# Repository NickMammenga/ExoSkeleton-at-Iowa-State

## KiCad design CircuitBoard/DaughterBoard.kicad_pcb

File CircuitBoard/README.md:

# Exoskeleton control board documentation
## Created and written by Parker K
### 11/12/26

## Mother Board
The mother board has two primary jobs. It first takes in the 48V battery and distributes it to both motors while converting down to 5V for the rest of the board. It also contains the microcontroller that runs the control loop and takes in data from the sensors.

The power section uses a mostly stock example circuit from the LMR38020. This takes 48V down to 5V using a switching regulator. The only important thing to note is that the power filter capacitors on the battery need to be 100V rated, and the SMD fuses are set at 20amp. The motor has a nominal current draw of 8amps, and a peak of 24amps. By using a time delay 20amp fuse it makes sure the motors never draw enough current to damage them.

On the board design, the motors are connected by using large ground pours. It is recommended to use 2oz copper to manage the heat and current when manufacturing the boards but as of writing, this has not be tested.

The 5V is then routed into the 5Vin pin of the microcontroller which then converts it into 3.3V. (this uses the internal 5v to 3.3v regulator it has because of the USB). This saves space, but it means that the battery can not be plugged in at the same time the microcontroller is.

Finally there are some integrated sensors that the MCU draws from and CAN outputs. The motors work over CAN bus, and the Waveshare CAN module is used as the can transceiver.

## Daughter Board
In order to better fit the exoskeleton, the mother board is designed to be mounted on the back plate. The daughter board is then designed to house the user controls and be mounted on the front with a cable connecting the two. It contains an 8 position rotary switch, a potentiometer, and an RGB LED. The rotary switch can be used to change the mode the exoskeleton operates in, while the pot can control strength,

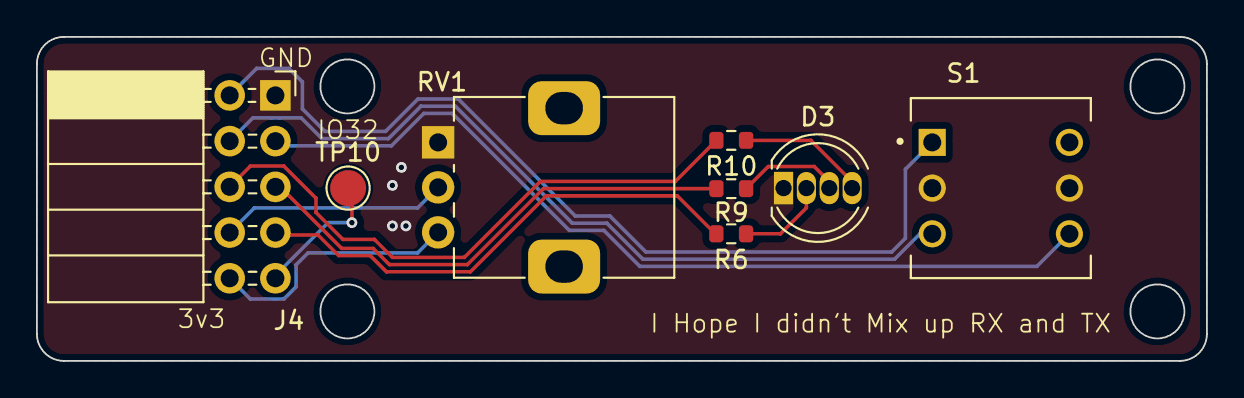
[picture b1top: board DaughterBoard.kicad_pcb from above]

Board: 2 copper layers, 65.0 x 18.0 mm, 8 parts (0 on the bottom side), 13 nets.

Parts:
D3: LED_KRGB; LED_D5.0mm-4_RGB
J4: Conn_01x10_Pin; PinSocket_2x05_P2.54mm_Horizontal
R6, R9, R10: 220; R_0603_1608Metric
RV1: 10KO; Potentiometer_Alps_RK09K_Single_Vertical
S1: RDS3-8S-1065-3-D; SW_RDS3-8S-1065-3-D
TP10: TestPoint; TestPoint_Pad_D2.0mm

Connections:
+3.3V: J4.10, RV1.3
GND: D3.1 (K), J4.1, RV1.1, S1.C1 (C), S1.C2 (C__1)
unnamed: D3.4 (BA), R10.1
unnamed: D3.3 (GA), R9.1
unnamed: D3.2 (RA), R6.1
unnamed: J4.2, S1.1
unnamed: J4.3, S1.2
unnamed: J4.4, S1.4
unnamed: J4.5, R9.2
unnamed: J4.6, R10.2
unnamed: J4.7, R6.2
unnamed: J4.8, RV1.2
unnamed: J4.9, TP10.1 (1_1)

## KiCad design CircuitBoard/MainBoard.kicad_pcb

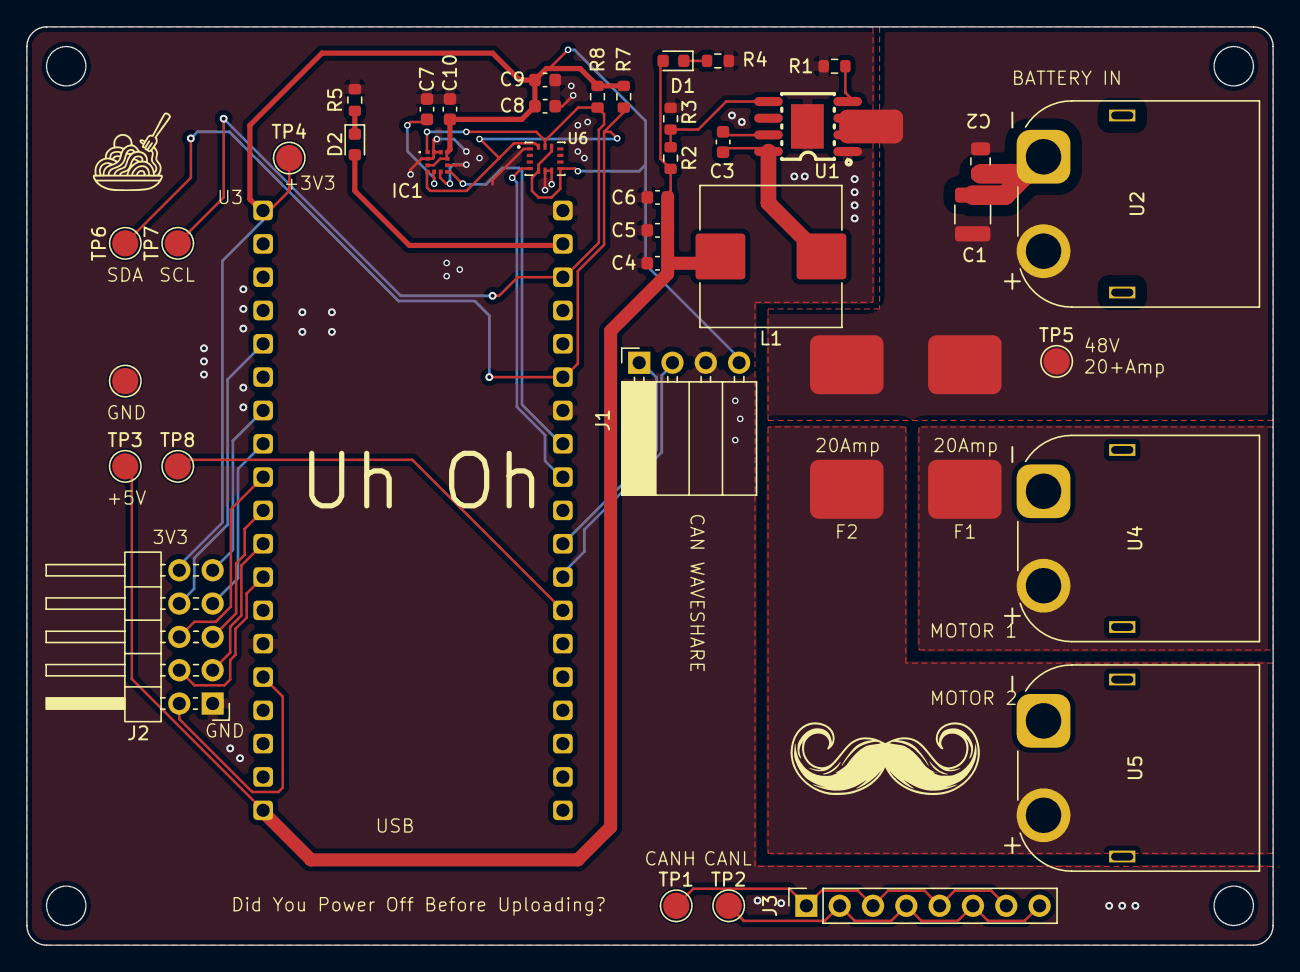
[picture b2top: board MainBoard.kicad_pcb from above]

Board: 2 copper layers, 95.0 x 70.0 mm, 40 parts (0 on the bottom side), 31 nets.

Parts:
C1: 4.7uF; C_1210_3225Metric
C2: 100nF; C_0805_2012Metric
C3, C8, C9, C10: 100nF; C_0603_1608Metric
C4, C5, C6: 22uF; C_0603_1608Metric
C7: 220nF; C_0603_1608Metric
D1, D2: LED; LED_0603_1608Metric
F1, F2: Fuse; SMDFuse MP012924
IC1: IIS2MDCTR
J1: Conn_01x04_Socket; PinSocket_1x04_P2.54mm_Horizontal
J2: Conn_01x10_Pin; PinHeader_2x05_P2.54mm_Horizontal
J3: Conn_01x08_Pin; PinSocket_1x08_P2.54mm_Vertical
L1: 15uH; L_Wuerth_HCI-1030
R1: 64.9kO; R_0603_1608Metric
R2: 100k; R_0603_1608Metric
R3: 24.9k; R_0603_1608Metric
R4, R5: 1k; R_0603_1608Metric
R7: 4.7k; R_0603_1608Metric
R8: 4,7k; R_0603_1608Metric
TP1, TP2, TP3, TP4, TP5, TP6, TP7, TP8: TestPoint; TestPoint_Pad_D2.0mm
U1: LMR38020SQDDARQ1; SOIC-8_L4.9-W3.9-P1.27-LS6.0-BL-EP3.4
U2, U4, U5: XT60; AMASS_XT60PW-M_1x02_P7.20mm_Horizontal
U3: ESP32 38Pin Slim
U6: BMI270; XDCR_BMI270

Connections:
48V: C1.1, C2.1, F1.2, F2.2, TP5.1 (1_1), U1.2 (EN), U1.3 (VIN), U2.2 (+)
+3.3V: C8.1, C9.1, C10.1, IC1.3 (CS), IC1.9 (VDD), IC1.10 (VDD_IO), J1.4, J2.10, R7.1, R8.1, TP4.1 (1_1), U3.1 (3.3V), U6.5 (VDDIO), U6.8 (VDD), U6.12 (CSB)
+5V: C4.1, C5.1, C6.1, D1.2 (A), L1.2, R2.1, TP3.1 (1_1), U3.19 (5.0V_In)
CANH: J3.1, J3.3, J3.5, J3.7, TP1.1 (1_1)
CANL: J3.2, J3.4, J3.6, J3.8, TP2.1 (1_1)
CRX: J1.2, U3.27 (IO16)
CTX: J1.1, U3.28 (IO17)
GND: C1.2, C2.2, C4.2, C5.2, C6.2, C7.1, C8.2, C9.2, C10.2, IC1.2 (NC_1), IC1.6 (GND_1), IC1.8 (GND_2), IC1.11 (NC_2), IC1.12 (NC_3), J1.3, J2.1, R1.2, R3.2, R4.2, R5.2, U1.1 (GND), U1.9 (EP), U2.1 (-), U3.14 (GND), U3.32 (GND), U3.38 (GND), U4.1 (-), U5.1 (-), U6.1 (SDO), U6.6 (GNDIO), U6.7 (GND)
IMUINT: U3.30 (IO18), U6.4 (INT1)
MAGDRDY: IC1.7 (INT/DRDY), U3.31 (IO19)
unnamed: D1.1 (K), R4.1
unnamed: D2.2 (A), U3.37 (IO23)
unnamed: D2.1 (K), R5.1
unnamed: C7.2, IC1.5 (C1)
unnamed: J2.2, U3.15 (IO13)
unnamed: J2.3, U3.11 (IO27)
unnamed: J2.4, U3.12 (IO14)
unnamed: J2.5, U3.10 (IO26)
unnamed: J2.6, U3.9 (IO25)
unnamed: J2.7, U3.8 (IO33)
unnamed: J2.8, U3.5 (IO34)
unnamed: J2.9, U3.7 (IO32)
unnamed: C3.1, U1.7 (BOOT)
unnamed: R2.2, R3.1, U1.5 (FB)
unnamed: R1.1, U1.4 (RT/SYNC)
unnamed: C3.2, L1.1, U1.8 (SW)
unnamed: TP8.1 (1_1), U3.26 (IO4)
unnamed: F1.1, U4.2 (+)
unnamed: F2.1, U5.2 (+)
SCL: IC1.1 (SCL/SPC), R8.2, TP7.1 (1_1), U3.36 (IO22), U6.13 (SCX)
SDA: IC1.4 (SDA/SDI/SDO), R7.2, TP6.1 (1_1), U3.33 (IO21), U6.14 (SDX)
